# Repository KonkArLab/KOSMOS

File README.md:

# KOSMOS
An underwater observation tool

Cette œuvre est mise à disposition selon les termes de la [Licence Creative Commons Attribution - Pas d’Utilisation Commerciale - Partage dans les Mêmes Conditions 4.0 International.](https://creativecommons.org/licenses/by-nc-sa/4.0/) L'auteur à mentionner est Konk Ar Lab et Ifremer

Le KOSMOS est un programme de sciences participatives née du partenariat atypique
entre une institution scientifique, l’Ifremer, et un Tiers Lieu, le Konk Ar Lab, Fablab de
Concarneau. Cette caméra d’observation de la faune et de la flore sous marine côtière a
permis de réunir autour d’un projet commun, acteurs de la recherche scientifique et de la
société civile.

La fabrication du KOSMOS au Konk Ar Lab est un formidable exemple d’intelligence
collective. Bénévoles et scientifiques collaborent main dans la main afin de concevoir cet
outil en s’assurant qu’il soit reproductible par tous, peu coûteux et scientifiquement
viable, c’est à dire répondant aux exigences du protocole scientifique STAVIRO déjà validé pour l’observation
et le suivi des écosystèmes côtiers.

Ce sont ces trois enjeux qui ont motivé Dominique Pelletier, directrice de recherche
Écologie et Modèles pour l’Halieutique (EMH), à se tourner vers le Konk Ar Lab. En effet,
Dominique a d’ores et déjà développé deux caméras utilisées à travers le monde : le
STAVIRO et le MICADO. Cependant, leur mode de fabrication est limitant et ne permet
pas à tout acteur ou potentiel utilisateur (institution scientifique, parc naturel marin, citoyen) de s’emparer du
projet alors même que les besoins d’évaluation et de suivi sont croissants. Le KOSMOS
offre donc une solution à ce qui semblait être une impasse.

L’Ifremer s’est tourné vers le FabLab de Concarneau en sa qualité de lieu de facilitation
sociale par le numérique. Le Konk Ar Lab, implanté sur le territoire de Concarneau
Cornouailles Agglomération (CCA), est un lieu réunissant tout type de publics locaux
autour de projets numériques et techniques venus de divers horizons. Ce projet est donc
un moyen innovant de partager ses connaissances tant sur des aspects techniques,
mécaniques que biologiques ou écologiques.

Découvrir, partager, sensibiliser sont les thèmes centraux du projet KOSMOS. Un
programme de sciences participatives visant à réunir plaisanciers et scientifiques autour
de l’utilisation de la caméra en mer, verra le jour en 2023. L’objectif est de permettre à tout
un chacun de collecter des vidéos lors de sorties en mer et de les analyser. En offrant
ainsi de nouvelles données aux scientifiques, les observateurs développent ou
approfondissent leur connaissance du milieu côtier et offrent la possibilité de suivre son
évolution sur le long terme.

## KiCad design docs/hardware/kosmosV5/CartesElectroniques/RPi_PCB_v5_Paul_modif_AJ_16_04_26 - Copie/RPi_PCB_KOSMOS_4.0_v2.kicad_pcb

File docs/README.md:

# KOSMOS 3.0

Le KOSMOS est un programme de sciences participatives née du partenariat atypique
entre une institution scientifique, l’Ifremer, et un Tiers Lieu, le Konk Ar Lab, Fablab de
Concarneau. Cette caméra d’observation de la faune et de la flore sous marine côtière a
permis de réunir autour d’un projet commun, acteurs de la recherche scientifique et de la
société civile.

La fabrication du KOSMOS au Konk Ar Lab est un formidable exemple d’intelligence
collective. Bénévoles et scientifiques collaborent main dans la main afin de concevoir cet
outil en s’assurant qu’il soit reproductible par tous, peu coûteux et scientifiquement
viable, c’est à dire répondant au protocole scientifique déjà en vigueur pour l’observation
et le suivi des écosystèmes côtiers.

Ce sont ces trois enjeux qui ont motivé Dominique Pelletier, directrice de recherche
Écologie et Modèles pour l’Halieutique (EMH), à se tourner vers le Konk Ar Lab. En effet,
Dominique a d’ores et déjà développé deux caméras utilisées à travers le monde : le
STAVIRO et le MICADO. Cependant, leur mode de fabrication est limitant et ne permet
pas à tout acteur (institution scientifique, parc naturel marin, citoyen) de s’emparer du
projet alors même que nos besoins d’évaluation et de suivis sont croissant. Le KOSMOS
offre donc une solution non négligeable a ce qui semblait être une impasse.

L’Ifremer s’est tourné vers le FabLab de Concarneau en sa qualité de lieu de facilitation
sociale par le numérique. Le Konk Ar Lab, implanté sur le territoire de Concarneau
Cornouailles Agglomération (CCA), est un lieu réunissant tout type de publics locaux
autour de projets numériques et techniques venus de divers horizons. Ce projet est donc
un moyen innovant de partager ses connaissances tant sur des aspects techniques,
mécaniques que biologiques ou écologiques.

Découvrir, partager, sensibiliser sont les thèmes centraux du projet KOSMOS. Un
programme de sciences participatives visant à réunir plaisanciers et scientifiques autour
de l’utilisation de la caméra en mer, verra le jour en 2023. L’objectif est de permettre à tout
un chacun de collecter des vidéos lors de sorties en mer et de les analyser. En offrant
ainsi de nouvelles données aux scientifiques, les observateurs développent ou

approfondissent leur connaissances du milieu côtier et offrent la possibilité de suivre son
évolution sur le long terme.

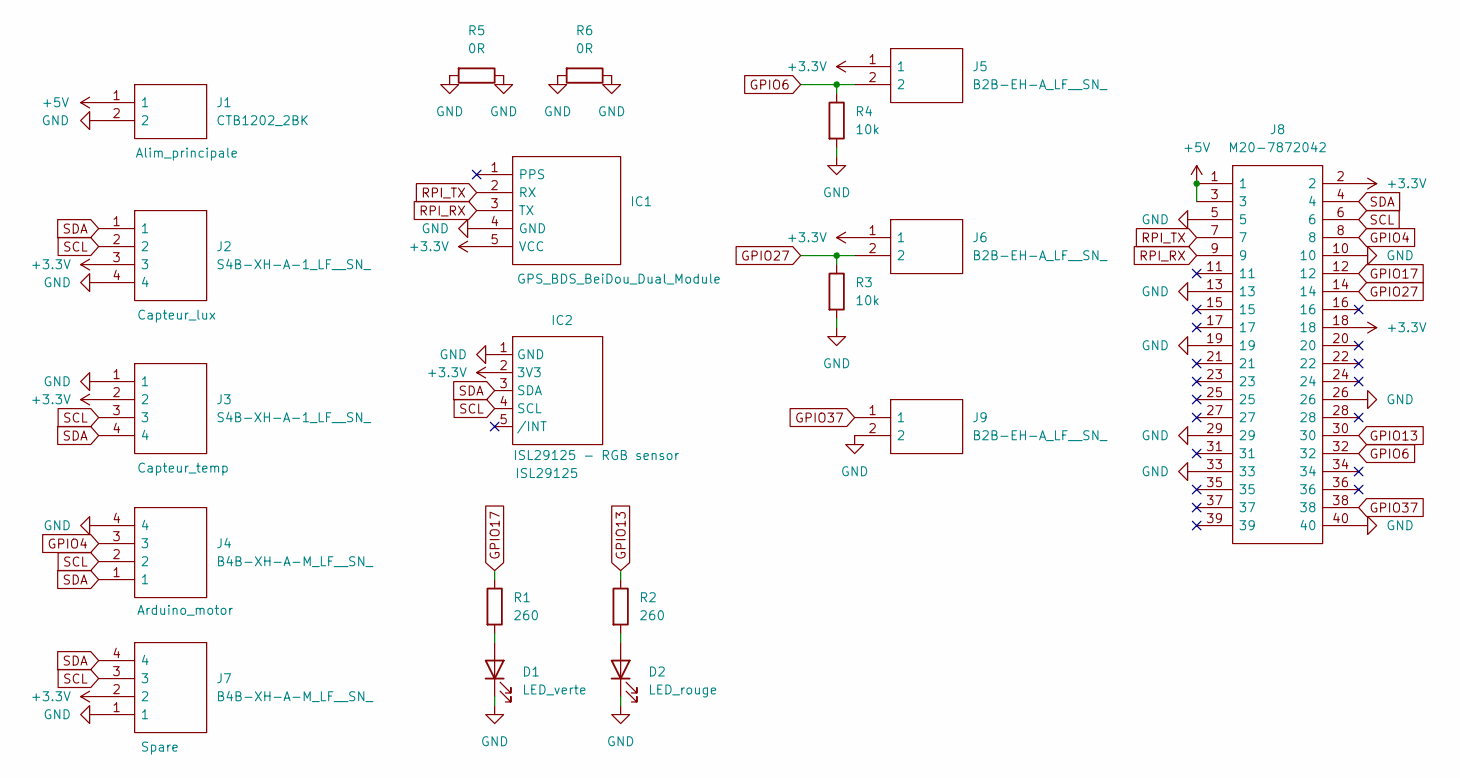
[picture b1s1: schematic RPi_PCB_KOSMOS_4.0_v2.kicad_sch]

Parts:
D1: LED_verte; LED_D5.0mm_IRBlack
D2: LED_rouge; LED_D5.0mm_IRBlack
IC1: GPS_BDS_BeiDou_Dual_Module
IC2: ISL29125 - RGB sensor; ISL29125
J1: CTB1202_2BK; CTB12022BK; Manufacturer_Part_Number CTB1202/2BK
J2, J3: S4B-XH-A-1_LF__SN_; S4BXHA1LFSN; Manufacturer_Part_Number S4B-XH-A-1(LF)(SN); Mouser Part Number N/A
J4, J7: B4B-XH-A-M_LF__SN_; B4BXHAMLFSN; Manufacturer_Part_Number B4B-XH-A-M(LF)(SN); Mouser Part Number 306-B4BXHAMLFSN
J5, J6, J9: B2B-EH-A_LF__SN_; B2BEHALFSN; Manufacturer_Part_Number B2B-EH-A(LF)(SN); Mouser Part Number N/A
J8: M20-7872042; M207872042; Manufacturer_Part_Number M20-7872042; Mouser Part Number 855-M20-7872042
R1, R2: 260; R_Axial_DIN0207_L6.3mm_D2.5mm_P10.16mm_Horizontal
R3, R4: 10k; R_Axial_DIN0207_L6.3mm_D2.5mm_P10.16mm_Horizontal
R5, R6: 0R; R_Axial_DIN0207_L6.3mm_D2.5mm_P10.16mm_Horizontal

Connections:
+3.3V: IC1.5 (VCC), IC2.2 (3V3), J2.3, J3.2, J5.1, J6.1, J7.2, J8.2, J8.18
+5V: J1.1, J8.1, J8.3
GND: D1.1 (K), D2.1 (K), IC1.4 (GND), IC2.1 (GND), J1.2, J2.4, J3.1, J4.4, J7.1, J8.5, J8.10, J8.13, J8.19, J8.26, J8.29, J8.33, J8.40, J9.2, R3.2, R4.2, R5.1, R5.2, R6.1, R6.2
GPIO4: J4.3, J8.8
GPIO6: J5.2, J8.32, R4.1
GPIO13: J8.30, R2.1
GPIO17: J8.12, R1.1
GPIO27: J6.2, J8.14, R3.1
GPIO37: J8.38, J9.1
unnamed: D1.2 (A), R1.2
unnamed: D2.2 (A), R2.2
RPI_RX: IC1.3 (TX), J8.9
RPI_TX: IC1.2 (RX), J8.7
SCL: IC2.4 (SCL), J2.2, J3.3, J4.2, J7.3, J8.6
SDA: IC2.3 (SDA), J2.1, J3.4, J4.1, J7.4, J8.4

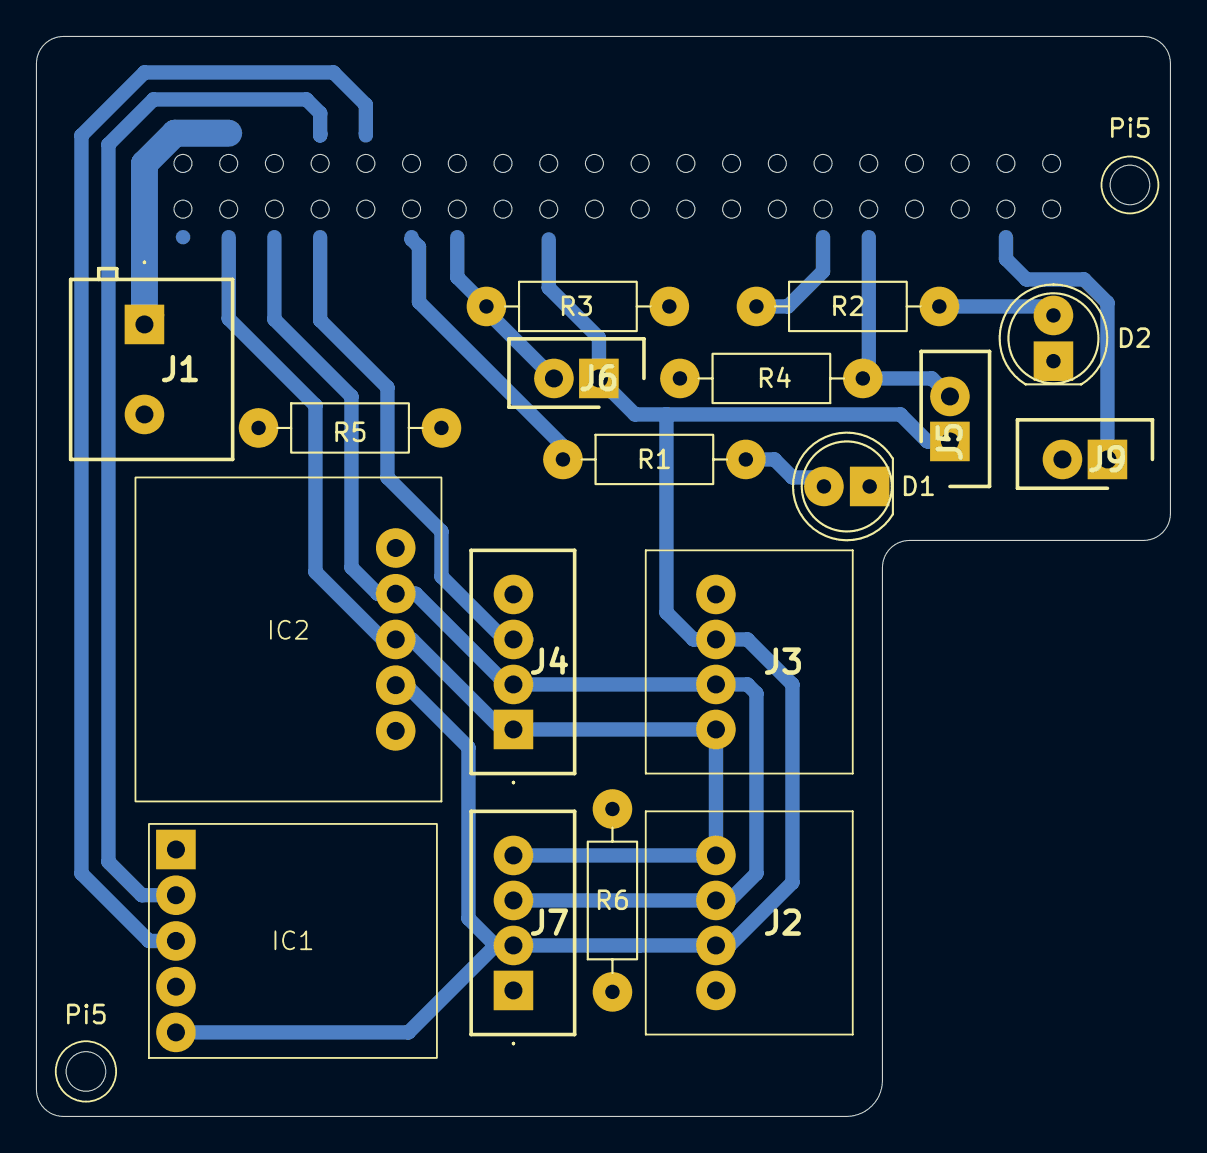
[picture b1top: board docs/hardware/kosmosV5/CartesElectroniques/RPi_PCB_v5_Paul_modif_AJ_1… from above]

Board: 2 copper layers, 63.0 x 60.0 mm, 21 parts (1 on the bottom side), 15 nets.

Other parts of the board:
Pi5, Pi5#2: MountingHole_2.2mm_M2

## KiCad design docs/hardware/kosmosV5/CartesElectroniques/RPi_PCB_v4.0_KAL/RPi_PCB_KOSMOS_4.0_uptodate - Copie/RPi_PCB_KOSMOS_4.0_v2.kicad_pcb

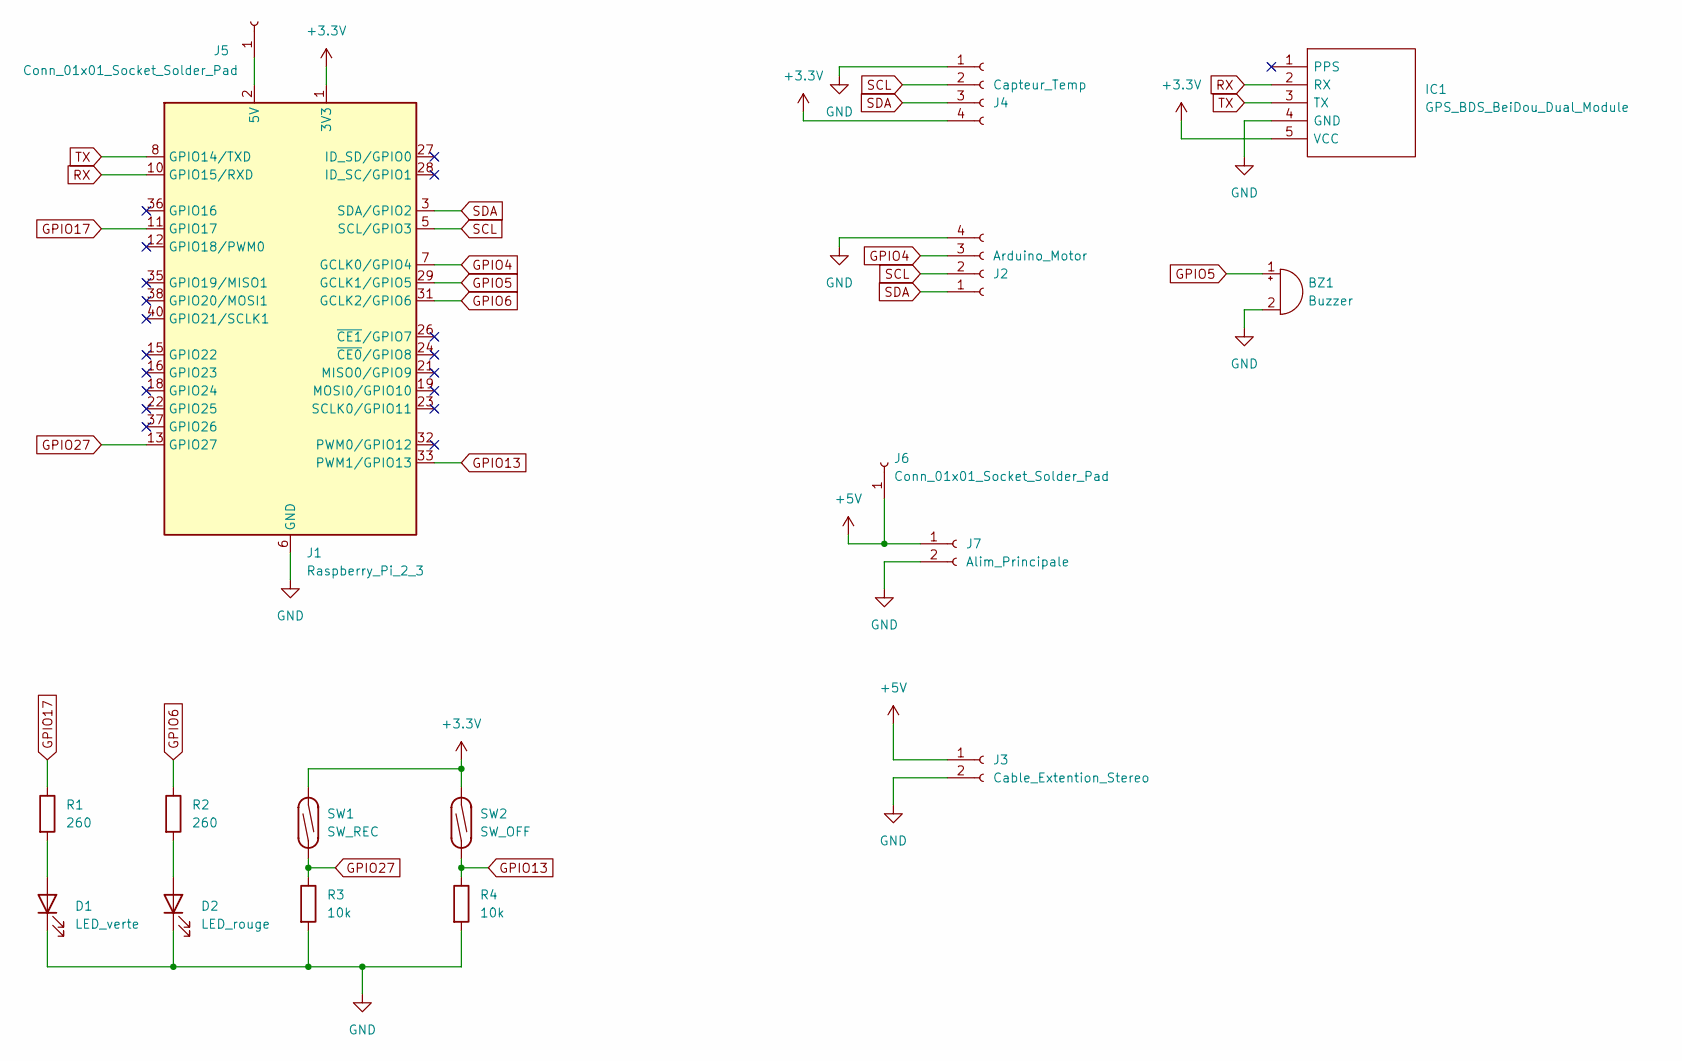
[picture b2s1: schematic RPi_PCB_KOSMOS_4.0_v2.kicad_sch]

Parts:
BZ1: Buzzer; Buzzer_D16.8_H8.2_P10_v2.2
D1: LED_verte; LED_D5.0mm_v2.2mm
D2: LED_rouge; LED_D5.0mm_v2.2mm
IC1: GPS_BDS_BeiDou_Dual_Module; GPS_BDS_BeiDou_Dual_Module_v2.2mm
J1: Raspberry_Pi_2_3; PinSocket_2x20_P2.54mm_Vertical_pad2.2mm
J2: Arduino_Motor; JST_EH_S4B-EH_1x04_P2.50mm_Horizontal_kosmos
J3: Cable_Extention_Stereo; JST_EH_S2B-EH_1x02_P2.50mm_Horizontal_kosmos
J4: Capteur_Temp; JST_EH_S4B-EH_1x04_P2.50mm_Horizontal_kosmos
J5, J6: Conn_01x01_Socket_Solder_Pad; TestPoint_Pad_4.0x4.0mm_KOSMOS
J7: Alim_Principale; TerminalBlock_bornier-2_P5.08mm_v3mm
R1, R2: 260; R_Axial_DIN0207_L6.3mm_D2.5mm_P10.16mm_Horizontal_v2.2mm
R3, R4: 10k; R_Axial_DIN0207_L6.3mm_D2.5mm_P10.16mm_Horizontal_v2.2mm
SW1: SW_REC; R_Axial_DIN0207_L6.3mm_D2.5mm_P13.24mm_Horizontal_v2mm
SW2: SW_OFF; R_Axial_DIN0207_L6.3mm_D2.5mm_P13.24mm_Horizontal_v2mm

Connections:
+3.3V: IC1.5 (VCC), J1.1 (3V3), J1.17 (3V3), J4.4, SW1.2, SW2.2
+5V: J3.1, J6.1, J7.1
GND: BZ1.2 (-), D1.1 (K), D2.1 (K), IC1.4 (GND), J1.6 (GND), J1.9 (GND), J1.14 (GND), J1.20 (GND), J1.25 (GND), J1.30 (GND), J1.34 (GND), J1.39 (GND), J2.4, J3.2, J4.1, J7.2, R3.2, R4.2
GPIO4: J1.7 (GCLK0/GPIO4), J2.3
GPIO5: BZ1.1 (+), J1.29 (GCLK1/GPIO5)
GPIO6: J1.31 (GCLK2/GPIO6), R2.1
GPIO13: J1.33 (PWM1/GPIO13), R4.1, SW2.1
GPIO17: J1.11 (GPIO17), R1.1
GPIO27: J1.13 (GPIO27), R3.1, SW1.1
unnamed: D1.2 (A), R1.2
unnamed: D2.2 (A), R2.2
unnamed: J1.2 (5V), J1.4 (5V), J5.1
RX: IC1.2 (RX), J1.10 (GPIO15/RXD)
SCL: J1.5 (SCL/GPIO3), J2.2, J4.2
SDA: J1.3 (SDA/GPIO2), J2.1, J4.3
TX: IC1.3 (TX), J1.8 (GPIO14/TXD)

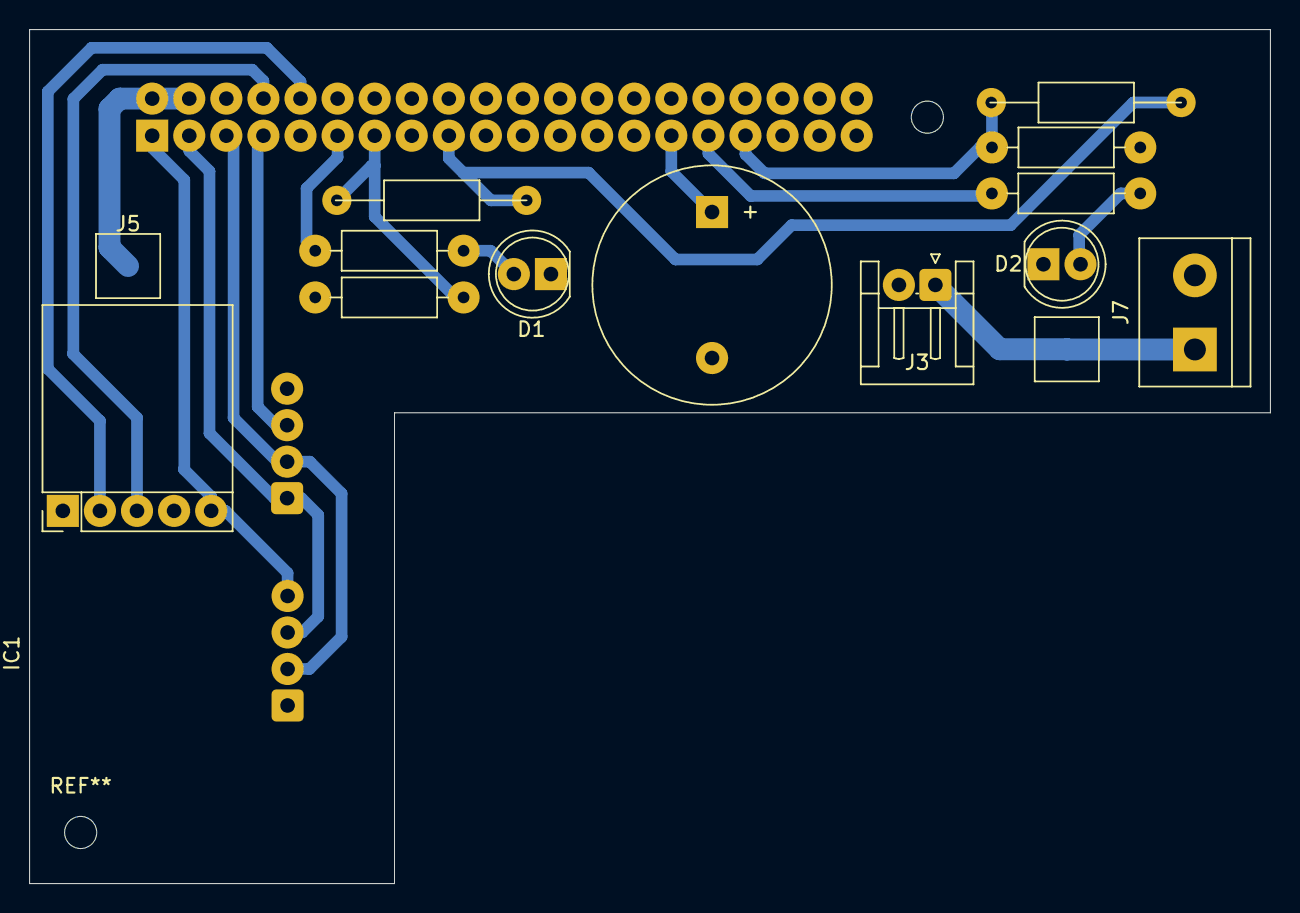
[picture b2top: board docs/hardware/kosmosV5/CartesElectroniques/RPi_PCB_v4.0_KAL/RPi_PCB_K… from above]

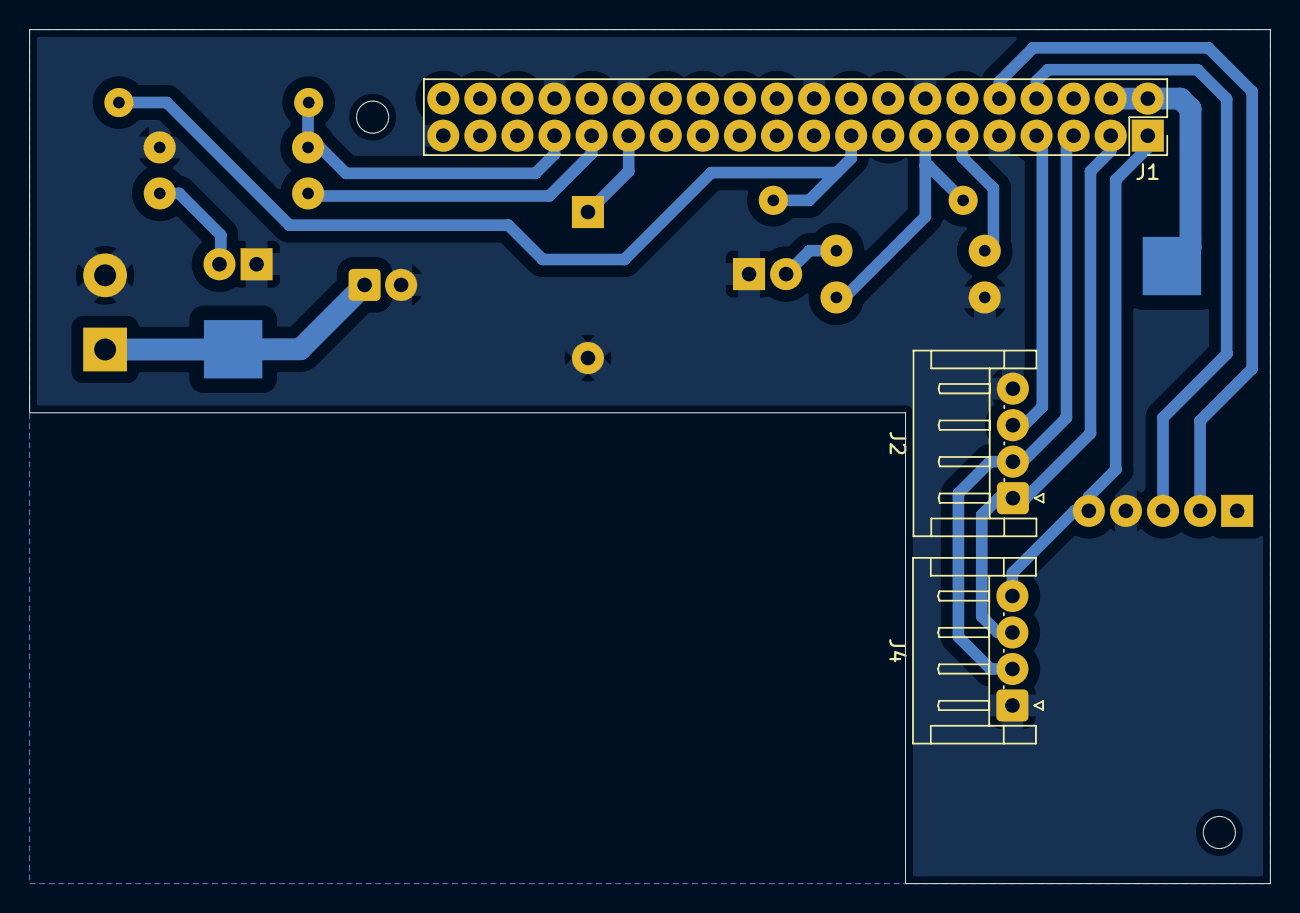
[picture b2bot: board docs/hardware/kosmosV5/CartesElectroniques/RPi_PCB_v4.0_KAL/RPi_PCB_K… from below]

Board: 2 copper layers, 85.0 x 58.5 mm, 17 parts (3 on the bottom side), 16 nets.

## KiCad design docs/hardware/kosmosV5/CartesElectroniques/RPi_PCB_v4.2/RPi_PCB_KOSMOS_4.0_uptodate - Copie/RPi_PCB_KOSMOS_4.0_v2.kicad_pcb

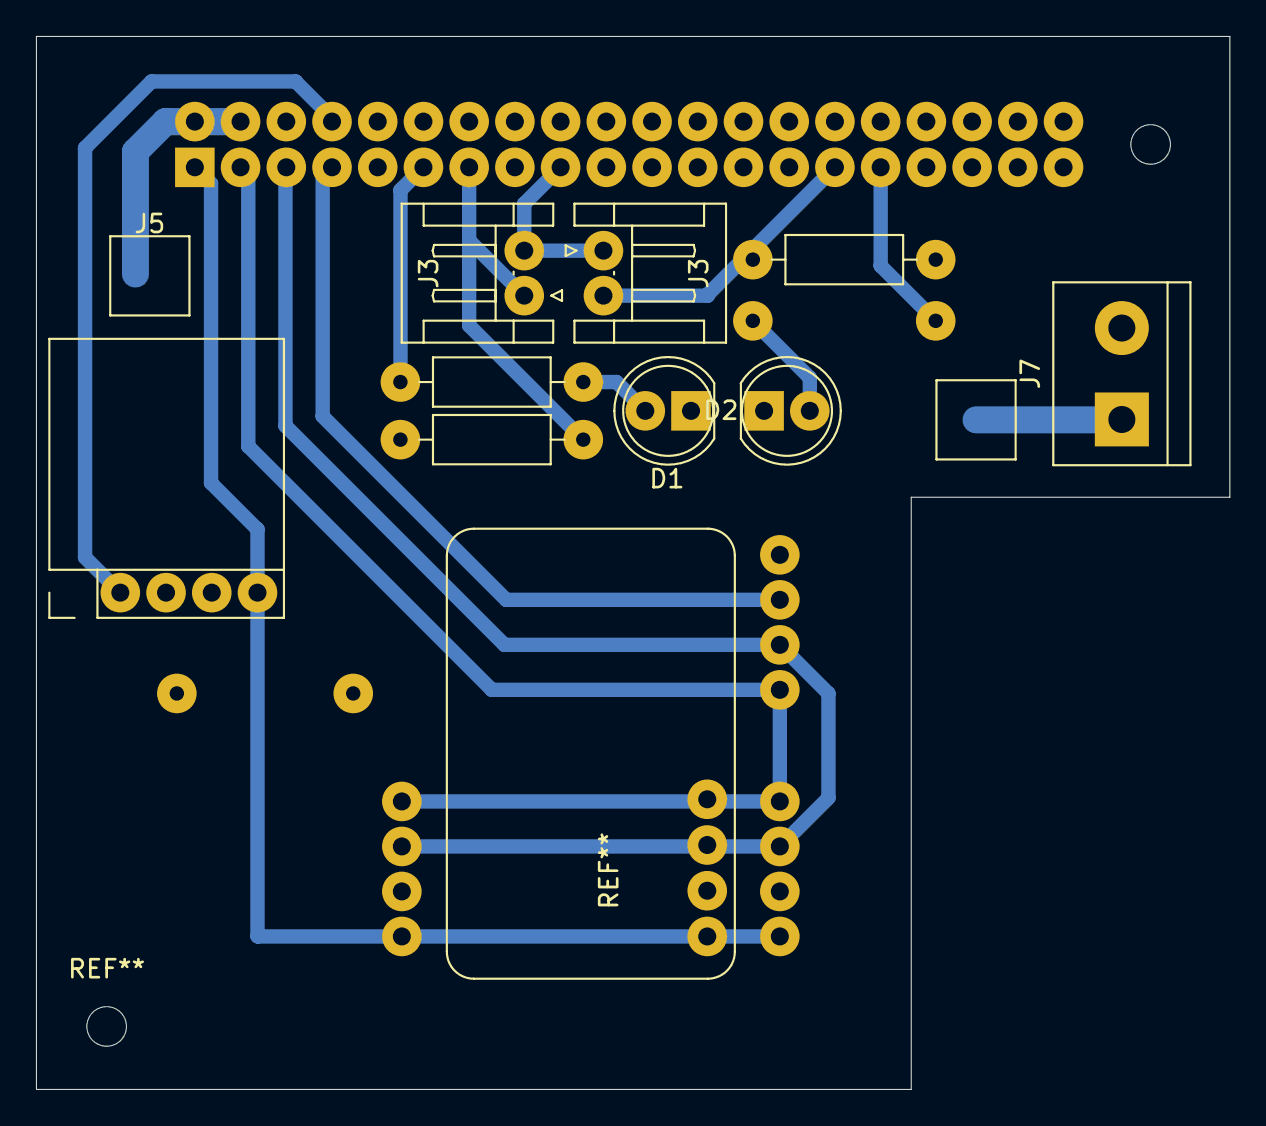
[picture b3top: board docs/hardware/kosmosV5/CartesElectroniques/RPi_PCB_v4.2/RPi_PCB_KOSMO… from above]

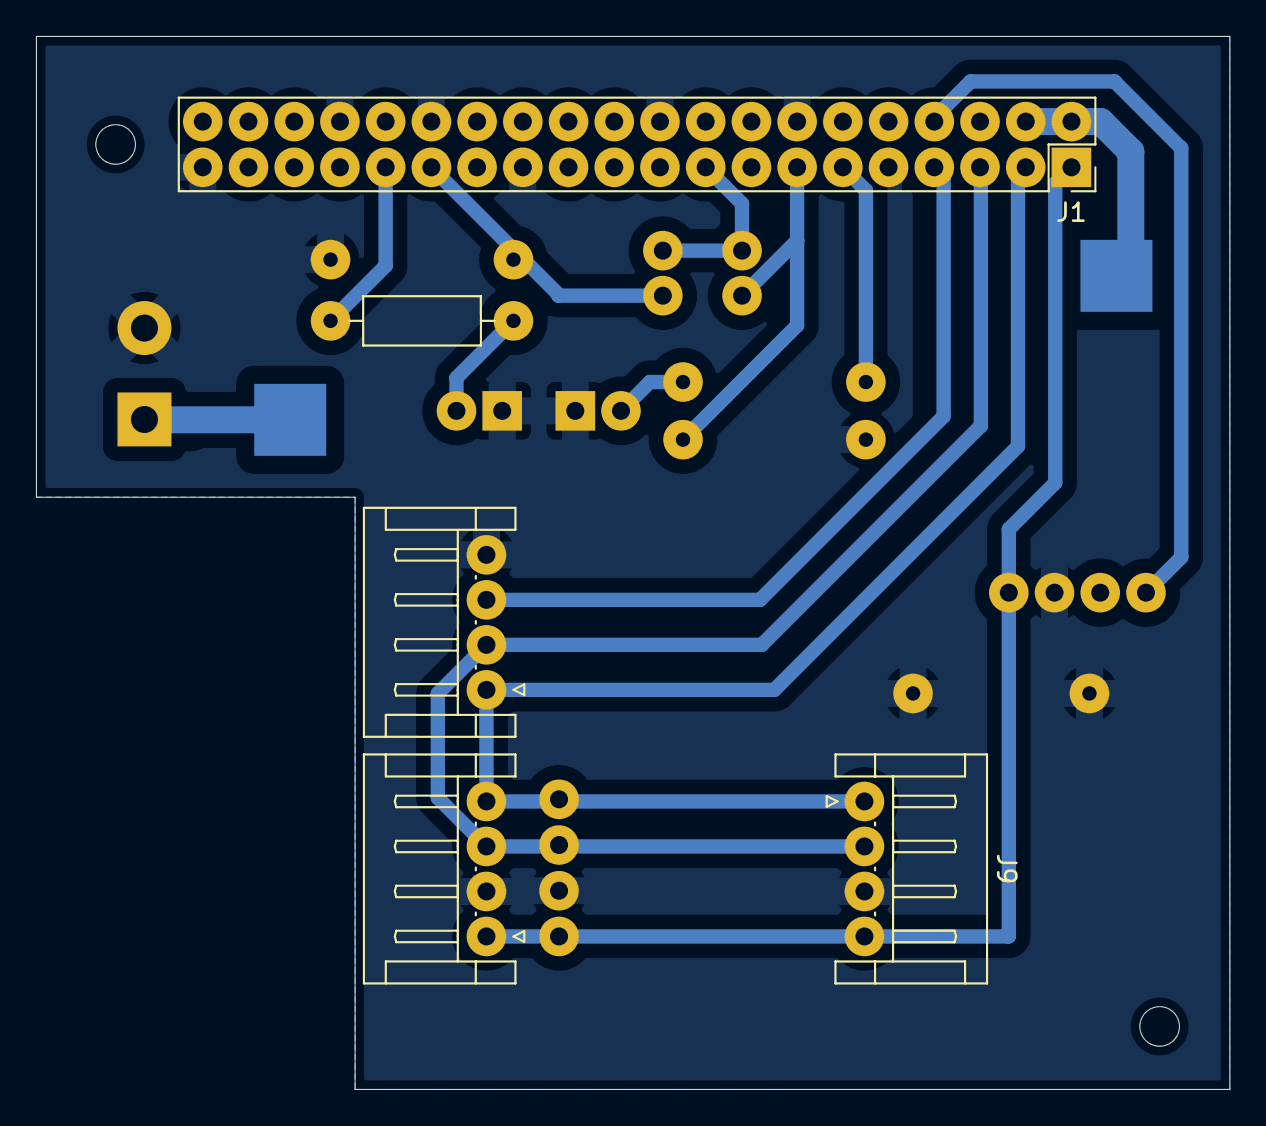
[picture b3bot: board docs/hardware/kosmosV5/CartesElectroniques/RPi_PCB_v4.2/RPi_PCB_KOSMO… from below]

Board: 2 copper layers, 66.3 x 58.5 mm, 16 parts (5 on the bottom side), 15 nets.

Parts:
D1: LED_verte; LED_D5.0mm_v2.2mm
D2: LED_rouge; LED_D5.0mm_v2.2mm
IC1: Module_GPS; GPS_BDS_BeiDou_Dual_Module_v2.2mm
J1: Raspberry_Pi_2_3; PinSocket_2x20_P2.54mm_Vertical_pad2.2mm
J2: Arduino_Motor; JST_EH_S4B-EH_1x04_P2.50mm_Horizontal_kosmos
J3, J3#2: ILS 1; JST_EH_S2B-EH_1x02_P2.50mm_Horizontal_kosmos
J4: Capteur_Temp; JST_EH_S4B-EH_1x04_P2.50mm_Horizontal_kosmos
J5, J6: Conn_01x01_Socket_Solder_Pad; TestPoint_Pad_4.0x4.0mm_KOSMOS
J7: Alim_Principale; TerminalBlock_bornier-2_P5.08mm_v3mm
J9: Capteur_Lux; JST_EH_S4B-EH_1x04_P2.50mm_Horizontal_kosmos
R1, R2: 260; R_Axial_DIN0207_L6.3mm_D2.5mm_P10.16mm_Horizontal_v2.2mm
R3, R4: 10k; R_Axial_DIN0207_L6.3mm_D2.5mm_P10.16mm_Horizontal_v2.2mm

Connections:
+3.3V: IC1.5 (VCC), J1.1 (3V3), J1.17 (3V3), J3.2, J3#2.1, J4.1, J9.4
+5V: J6.1, J7.1
GND: D1.1 (K), D2.1 (K), IC1.4 (GND), J1.6 (GND), J1.9 (GND), J1.14 (GND), J1.20 (GND), J1.25 (GND), J1.30 (GND), J1.34 (GND), J1.39 (GND), J2.4, J4.2, J7.2, J9.3, R3.2, R4.2
GPIO4: J1.7 (GCLK0/GPIO4), J2.3
GPIO5: J1.29 (GCLK1/GPIO5), J3#2.2, R4.1
GPIO6: J1.31 (GCLK2/GPIO6), R2.1
GPIO17: J1.11 (GPIO17), R1.1
GPIO27: J1.13 (GPIO27), J3.1, R3.1
unnamed: D1.2 (A), R1.2
unnamed: D2.2 (A), R2.2
unnamed: J1.2 (5V), J1.4 (5V), J5.1
RX: IC1.3 (TX), J1.10 (GPIO15/RXD)
SCL: J1.5 (SCL/GPIO3), J2.2, J4.3, J9.2
SDA: J1.3 (SDA/GPIO2), J2.1, J4.4, J9.1
TX: IC1.2 (RX), J1.8 (GPIO14/TXD)

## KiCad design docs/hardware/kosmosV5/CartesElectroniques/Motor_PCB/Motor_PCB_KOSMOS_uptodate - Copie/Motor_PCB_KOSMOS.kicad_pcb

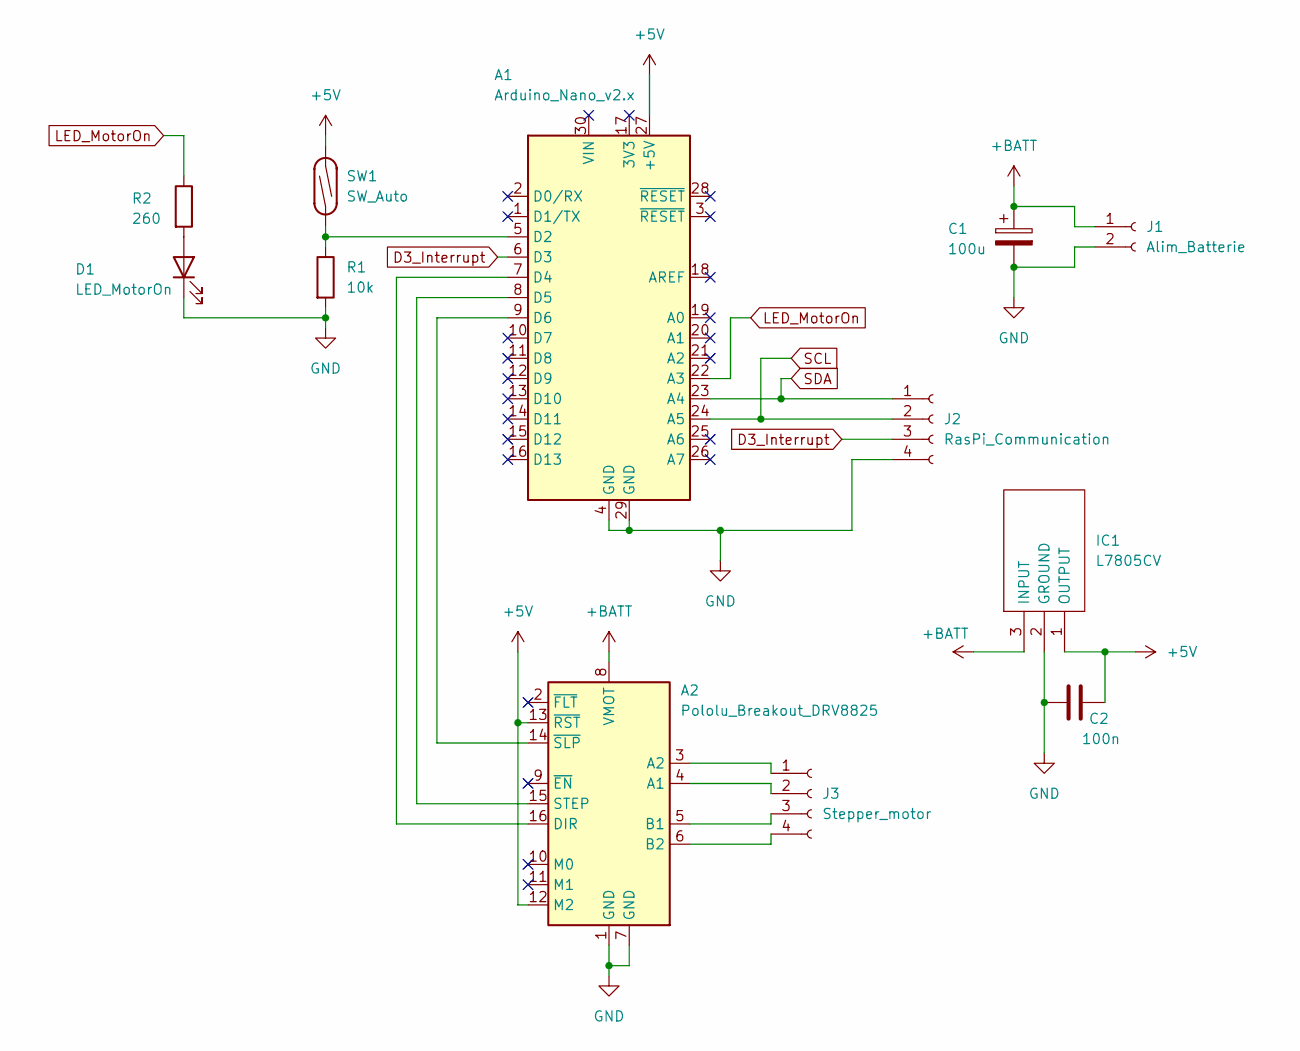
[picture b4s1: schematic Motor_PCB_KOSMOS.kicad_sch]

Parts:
A1: Arduino_Nano_v2.x; Arduino_Nano_v2.2mm
A2: Pololu_Breakout_DRV8825; Pololu_Breakout-16_15.2x20.3mm_v2.2mm
C1: 100u; CP_Radial_D5.0mm_P2.50mm_v2.2mm
C2: 100n; C_Rect_L7.0mm_W2.5mm_P5.00mm_v2.2mm
D1: LED_MotorOn; LED_D5.0mm_v2.2mm
IC1: L7805CV; L7805CV_v2.2mm; Manufacturer_Part_Number L7805CV; Mouser Part Number 511-L7805CV
J1: Alim_Batterie; TerminalBlock_bornier-2_P5.08mm_v3mm
J2: RasPi_Communication; JST_EH_B4B-EH-A_1x04_P2.50mm_Vertical_v2.2mm
J3: Stepper_motor; JST_EH_B4B-EH-A_1x04_P2.50mm_Vertical_v2.2mm
R1: 10k; R_Axial_DIN0207_L6.3mm_D2.5mm_P10.16mm_Horizontal_v2.2mm
R2: 260; R_Axial_DIN0207_L6.3mm_D2.5mm_P10.16mm_Horizontal_v2.2mm
SW1: SW_Auto; R_Axial_DIN0207_L6.3mm_D2.5mm_P15.24mm_Horizontal_v2mm

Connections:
+5V: A1.27 (+5V), A2.12 (M2), A2.13 (~RST), C2.2, IC1.1 (OUTPUT), SW1.2
+BATT: A2.8 (VMOT), C1.1, IC1.3 (INPUT), J1.1
D3_Interrupt: A1.6 (D3), J2.3
GND: A1.4 (GND), A1.29 (GND), A2.1 (GND), A2.7 (GND), C1.2, C2.1, D1.1 (K), IC1.2 (GROUND), J1.2, J2.4, R1.2
LED_MotorOn: A1.22 (A3), R2.1
unnamed: A1.5 (D2), R1.1, SW1.1
unnamed: A1.7 (D4), A2.16 (DIR)
unnamed: A1.8 (D5), A2.15 (STEP)
unnamed: A1.9 (D6), A2.14 (~SLP)
unnamed: A2.4 (A1), J3.2
unnamed: A2.3 (A2), J3.1
unnamed: A2.5 (B1), J3.3
unnamed: A2.6 (B2), J3.4
unnamed: D1.2 (A), R2.2
SCL: A1.24 (A5), J2.2
SDA: A1.23 (A4), J2.1

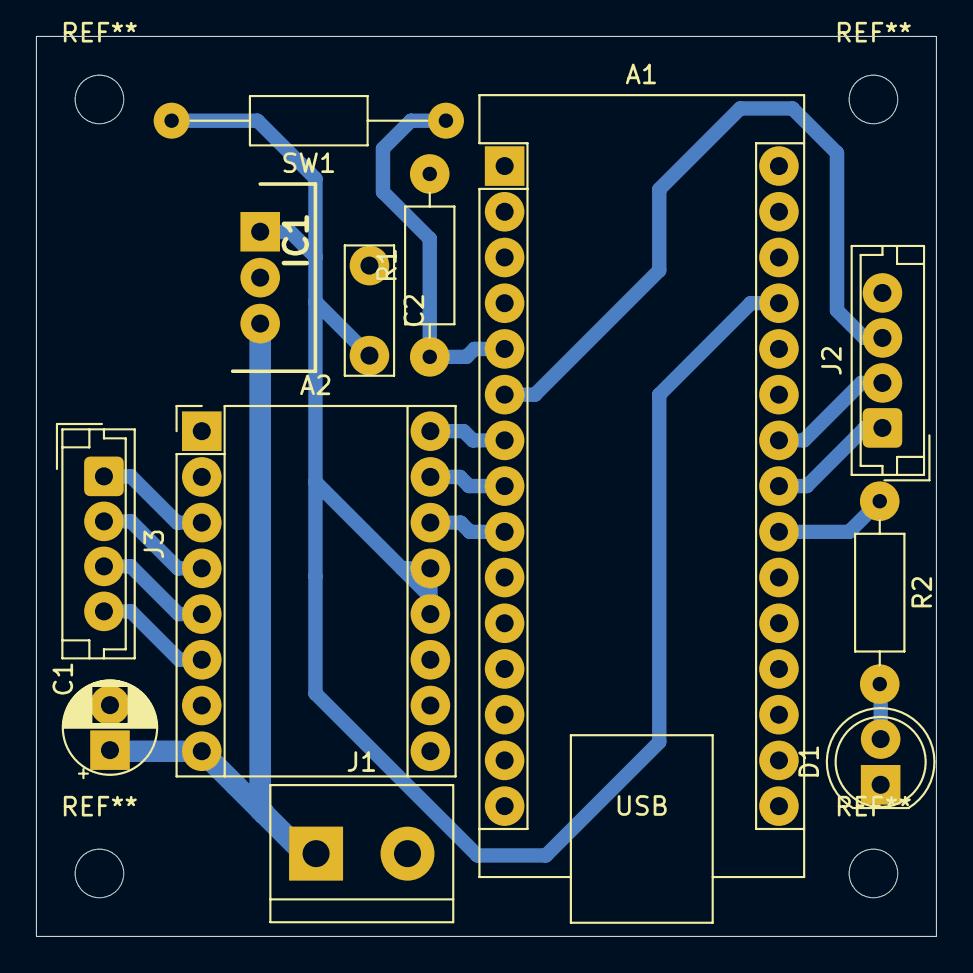
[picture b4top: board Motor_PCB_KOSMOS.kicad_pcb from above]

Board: 2 copper layers, 50.0 x 50.0 mm, 12 parts (0 on the bottom side), 16 nets.

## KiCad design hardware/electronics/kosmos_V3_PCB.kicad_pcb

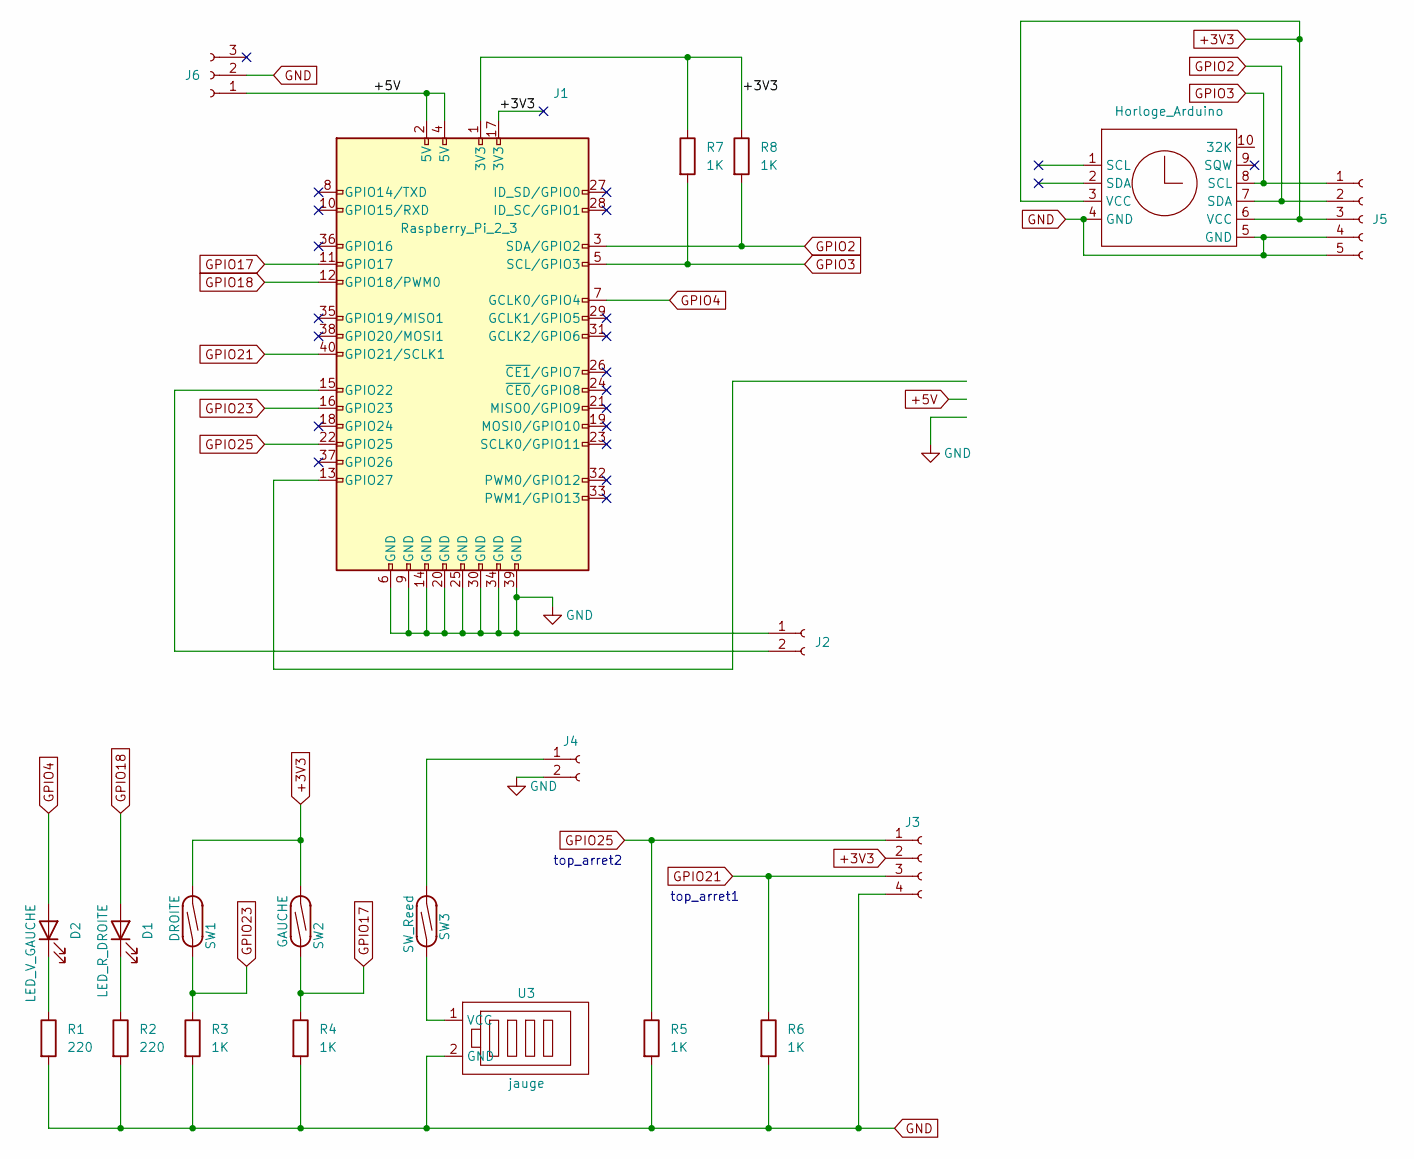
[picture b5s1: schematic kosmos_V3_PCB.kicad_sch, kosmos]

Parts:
D1: LED_R_DROITE; LED_D5.0mm_FlatTop
D2: LED_V_GAUCHE; LED_D5.0mm_FlatTop
J1: Raspberry_Pi_2_3; PinHeader_2x20_P2.54mm_Vertical
J2: CDE_ESP; PinHeader_1x02_P1.27mm_Vertical
J3: FACADE; PinHeader_1x04_P1.27mm_Vertical
J4: 12v_conv; PinHeader_1x02_P2.54mm_Vertical
J5: Conn_01x05_Female; PinHeader_1x05_P2.54mm_Vertical
J6: 5v_conv; PinHeader_1x03_P2.54mm_Vertical
R1, R2: 220; R_Axial_DIN0207_L6.3mm_D2.5mm_P10.16mm_Horizontal
R3, R4, R5, R6, R7, R8: 1K; R_Axial_DIN0207_L6.3mm_D2.5mm_P10.16mm_Horizontal
SW1: DROITE; R_Axial_DIN0207_L6.3mm_D2.5mm_P15.24mm_Horizontal
SW2: GAUCHE; R_Axial_DIN0207_L6.3mm_D2.5mm_P15.24mm_Horizontal
SW3: SW_Reed; R_Axial_DIN0207_L6.3mm_D2.5mm_P15.24mm_Horizontal
U1: Horloge_Arduino; Rtc_arduino
U3: jauge; Jauge_arduino

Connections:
+3V3: J1.1 (3V3), J1.17 (3V3), J3.2, J5.3, R7.1, R8.1, SW1.2, SW2.2, U1.3 (VCC), U1.6 (VCC)
+5V: J1.2 (5V), J1.4 (5V), J6.1; also elsewhere on the board
GND: J1.6 (GND), J1.9 (GND), J1.14 (GND), J1.20 (GND), J1.25 (GND), J1.30 (GND), J1.34 (GND), J1.39 (GND), J2.1, J3.4, J4.2, J5.4, J5.5, J6.2, R1.2, R2.2, R3.2, R4.2, R5.2, R6.2, U1.4 (GND), U1.5 (GND), U3.2 (GND); also elsewhere on the board
GPIO2: J1.3 (SDA/GPIO2), J5.2, R8.2, U1.7 (SDA)
GPIO3: J1.5 (SCL/GPIO3), J5.1, R7.2, U1.8 (SCL)
GPIO4: D2.2 (A), J1.7 (GCLK0/GPIO4)
GPIO17: J1.11 (GPIO17), R4.1, SW2.1
GPIO18: D1.2 (A), J1.12 (GPIO18/PWM0)
GPIO21: J1.40 (GPIO21/SCLK1), J3.3, R6.1
GPIO23: J1.16 (GPIO23), R3.1, SW1.1
GPIO25: J1.22 (GPIO25), J3.1, R5.1
unnamed: D1.1 (K), R2.1
unnamed: D2.1 (K), R1.1
unnamed: J1.15 (GPIO22), J2.2
unnamed 15: J4.1, SW3.2; also elsewhere on the board
unnamed: SW3.1, U3.1 (VCC)

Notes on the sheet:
top_arret2
top_arret1

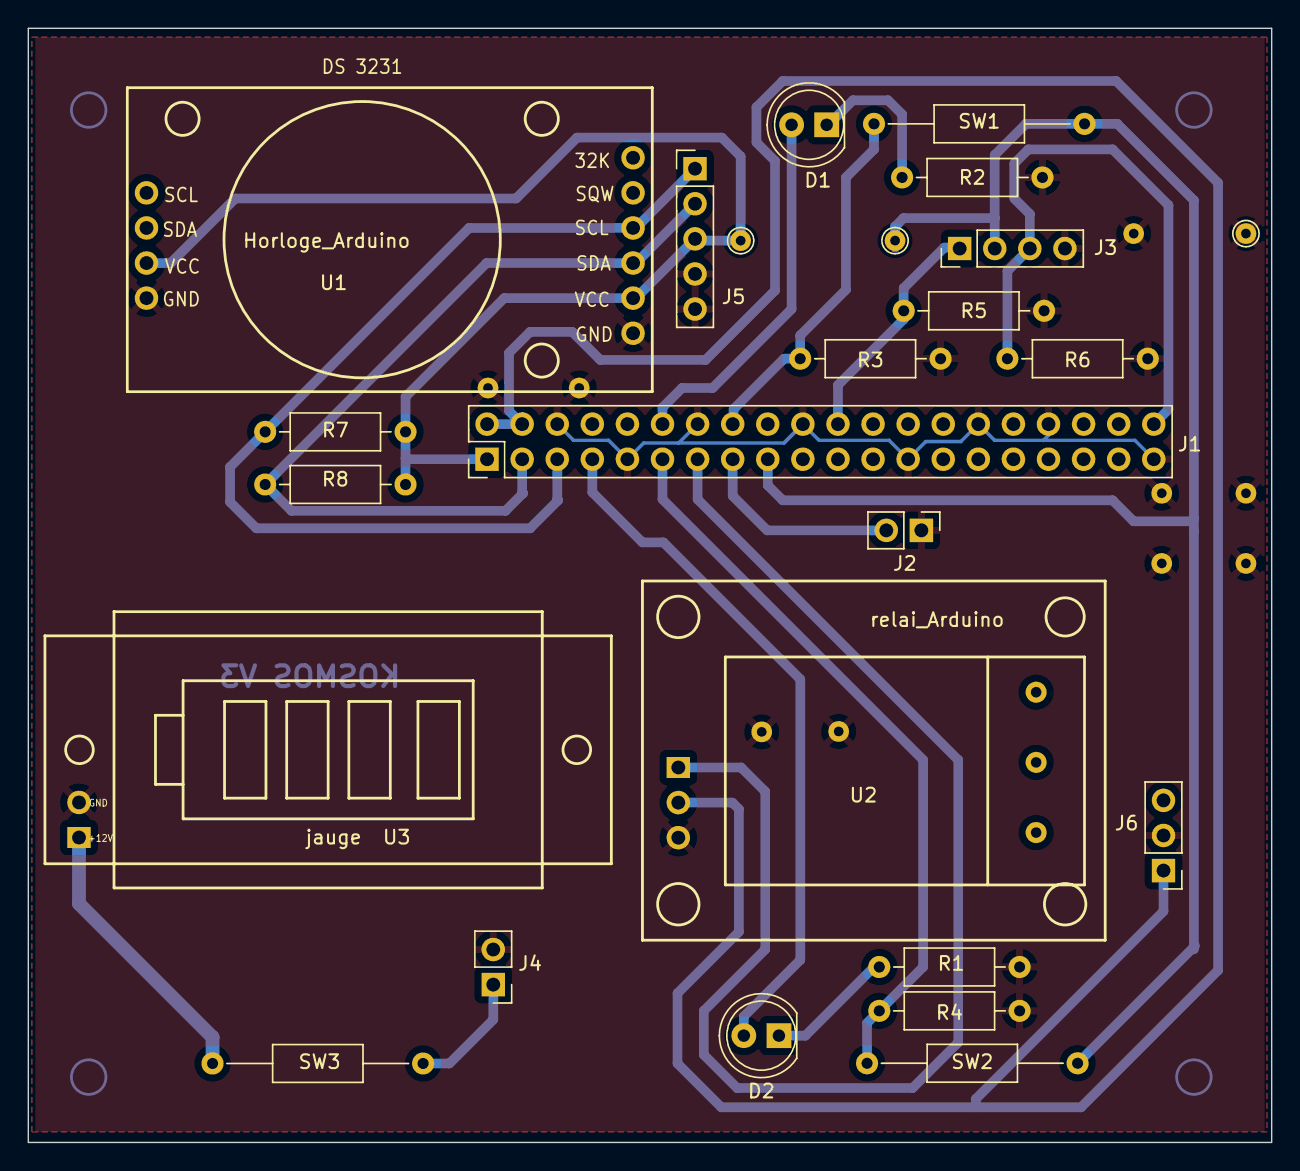
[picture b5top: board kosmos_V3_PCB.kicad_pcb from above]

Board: 2 copper layers, 90.0 x 80.6 mm, 22 parts (0 on the bottom side), 16 nets.

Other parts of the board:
J?: 12v_conv; PinHeader_1x02_P2.54mm_Vertical
J?#2: 5v_conv; PinHeader_1x03_P2.54mm_Vertical
U2: relai_Arduino; Relai_arduino

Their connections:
+5V: J?#2.1, U2.2 (VCC); also elsewhere on the board
GND: J?.2, J?#2.2, U2.3 (GND); also elsewhere on the board
unnamed 15: J?.1; also elsewhere on the board
